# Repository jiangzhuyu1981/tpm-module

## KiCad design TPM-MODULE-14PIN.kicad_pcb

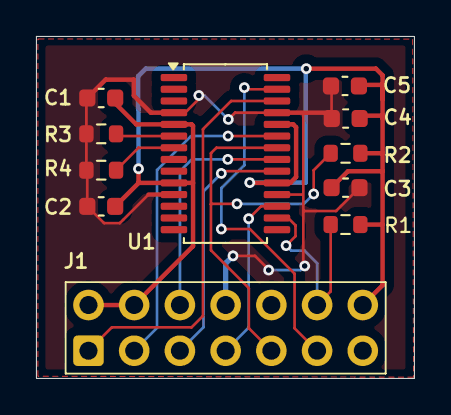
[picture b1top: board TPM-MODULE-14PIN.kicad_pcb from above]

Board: 2 copper layers, 21.0 x 19.0 mm, 11 parts (0 on the bottom side), 12 nets.

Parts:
C1: 1uF; C_0603_1608Metric
C2, C3, C4, C5: 100nF; C_0603_1608Metric
J1: Conn_02x07_Odd_Even; IDC-Header_2x07_P2.54mm_Horizontal
R1, R3, R4: 10K; R_0603_1608Metric
R2: 4.7K; R_0603_1608Metric
U1: SLB9665xT; TSSOP-28_4.4x9.7mm_P0.65mm

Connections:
+3V0: C1.2, C2.2, C3.2, C4.2, C5.2, J1.2 (+3V), J1.4 (+3V), J1.14 (+3V), R1.1, R2.1, U1.5 (VDD), U1.10 (VDD), U1.19 (VDD), U1.24 (VDD)
/CLK: J1.6 (PCICLK_TPM), U1.21 (LCLK)
/FRAME#: J1.9 (F_FRAME#), R2.2, U1.22 (~LFRAME)
/LAD0: J1.1 (F_LAD0), U1.26 (LAD0)
/LAD1: J1.3 (F_LAD1), U1.23 (LAD1)
/LAD2: J1.5 (F_LAD2), U1.20 (LAD2)
/LAD3: J1.7 (F_LAD3), U1.17 (LAD3)
/RESET#: J1.12 (PCIRST#), R1.2, U1.16 (~LRESET)
/SERIRQ: J1.11 (F_SERIRQ), U1.27 (SERIRQ)
GND: C1.1, C2.1, C3.1, C4.1, C5.1, J1.8 (GND), R3.1, R4.1, U1.4 (GND), U1.11 (GND), U1.18 (GND), U1.25 (GND)
unnamed: R3.2, U1.6 (GPIO)
unnamed: R4.2, U1.7 (PP)
